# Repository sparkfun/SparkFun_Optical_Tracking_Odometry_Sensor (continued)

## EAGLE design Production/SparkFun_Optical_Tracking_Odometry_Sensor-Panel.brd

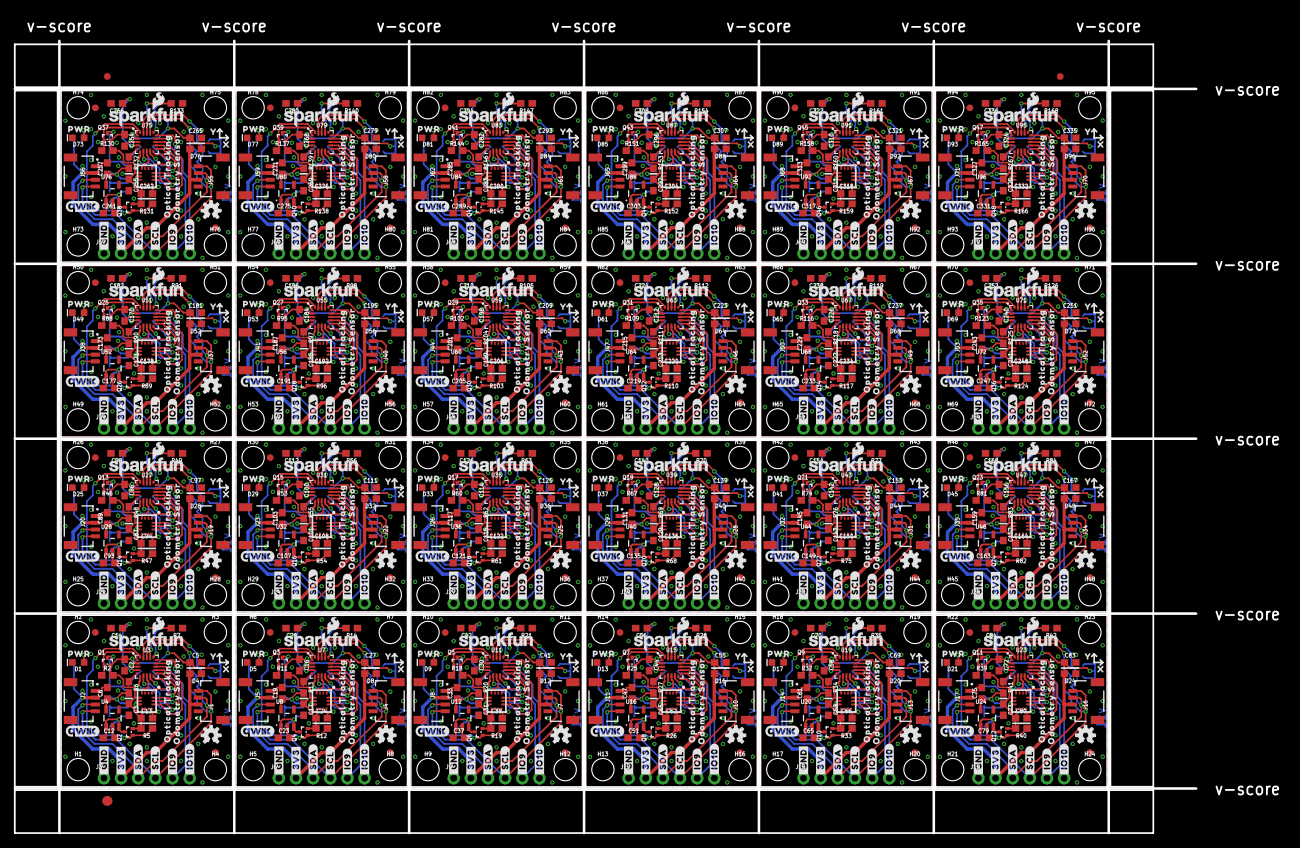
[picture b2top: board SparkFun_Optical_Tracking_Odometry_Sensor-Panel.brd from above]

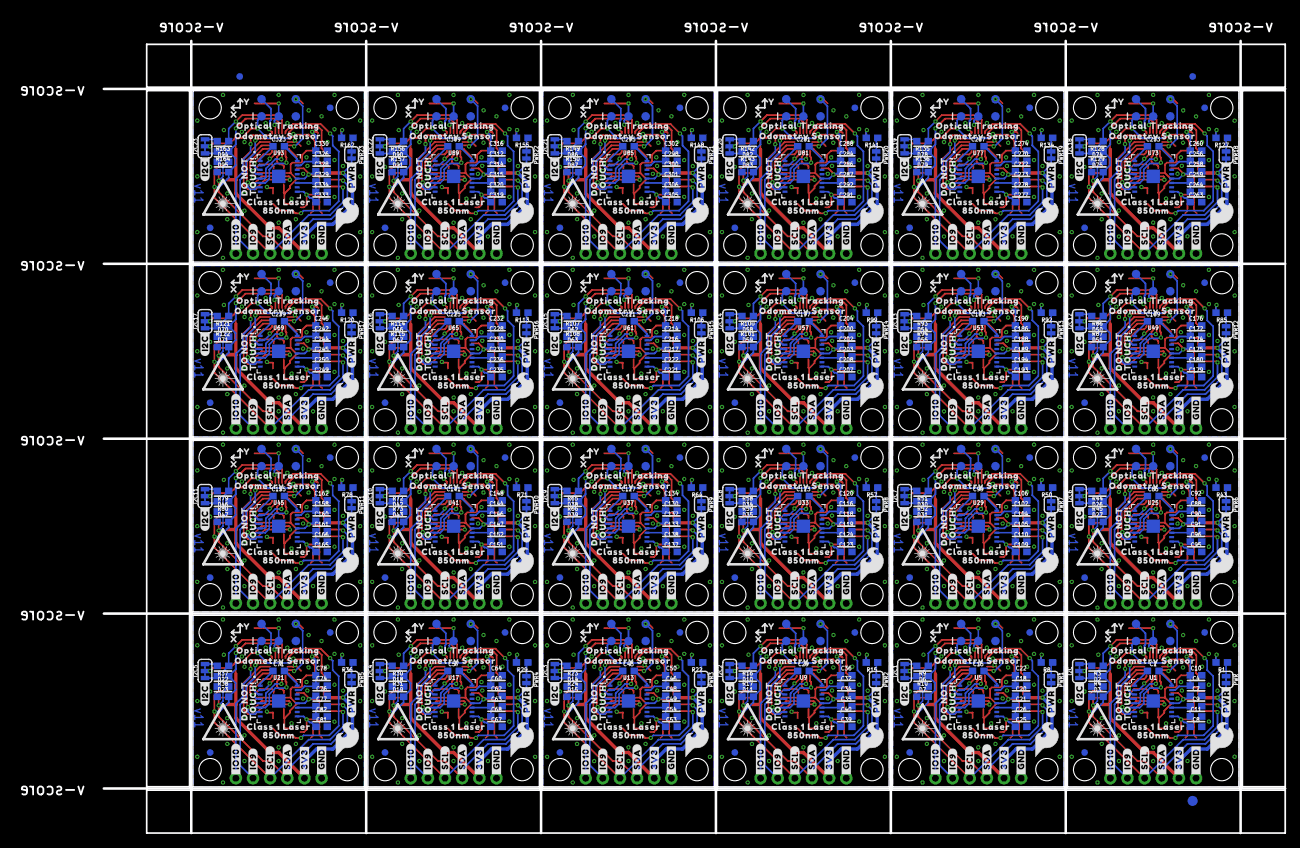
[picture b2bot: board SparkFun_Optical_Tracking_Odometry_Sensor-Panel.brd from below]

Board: 2 copper layers, 175.0 x 117.3 mm, 1830 parts (843 on the bottom side), 720 nets.

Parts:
C1, C15, C29, C43, C57, C71, C85, C99, C113, C127, C141, C155, C169, C183, C197, C211, C225, C239, C253, C267, C281, C295, C309, C323: 470pF; 0603
C2, C3, C4, C7, C8, C9, C13, C14, C16, C17, C18, C20, C21, C24, C25, C28, C30, C31, C32, C34, C35, C38, C39, C42, C44, C45, C46, C48, C49, C52, C53, C56, C58, C59, C60, C62, C63, C66, C67, C70, C72, C73, C74, C76, C77, C80, C81, C84, C86, C87, C88, C90, C91, C94, C95, C98, C100, C101, C102, C104, C105, C108, C109, C112, C114, C115, C116, C118, C119, C122, C123, C126, C128, C129, C130, C132, C133, C136, C137, C140, C142, C143, C144, C146, C147, C150, C151, C154, C156, C157, C158, C160, C161, C164, C165, C168, C170, C171, C172, C174, C175, C178, C179, C182, C184, C185, C186, C188, C189, C192, C193, C196, C198, C199, C200, C202, C203, C206, C207, C210, C212, C213, C214, C216, C217, C220, C221, C224, C226, C227, C228, C230, C231, C234, C235, C238, C240, C241, C242, C244, C245, C248, C249, C252, C254, C255, C256, C258, C259, C262, C263, C266, C268, C269, C270, C272, C273, C276, C277, C280, C282, C283, C284, C286, C287, C290, C291, C294, C296, C297, C298, C300, C301, C304, C305, C308, C310, C311, C312, C314, C315, C318, C319, C322, C324, C325, C326, C328, C329, C332, C333, C336: 0.1uF; 0603
C5, C6, C12, C19, C23, C27, C33, C37, C41, C47, C51, C55, C61, C65, C69, C75, C79, C83, C89, C93, C97, C103, C107, C111, C117, C121, C125, C131, C135, C139, C145, C149, C153, C159, C163, C167, C173, C177, C181, C187, C191, C195, C201, C205, C209, C215, C219, C223, C229, C233, C237, C243, C247, C251, C257, C261, C265, C271, C275, C279, C285, C289, C293, C299, C303, C307, C313, C317, C321, C327, C331, C335: 22uF; 0603
C10, C11, C22, C26, C36, C40, C50, C54, C64, C68, C78, C82, C92, C96, C106, C110, C120, C124, C134, C138, C148, C152, C162, C166, C176, C180, C190, C194, C204, C208, C218, C222, C232, C236, C246, C250, C260, C264, C274, C278, C288, C292, C302, C306, C316, C320, C330, C334: 4.7uF; 0603
D1, D5, D9, D13, D17, D21, D25, D29, D33, D37, D41, D45, D49, D53, D57, D61, D65, D69, D73, D77, D81, D85, D89, D93: Red; LED-0603
D2, D3, D4, D6, D7, D8, D10, D11, D12, D14, D15, D16, D18, D19, D20, D22, D23, D24, D26, D27, D28, D30, D31, D32, D34, D35, D36, D38, D39, D40, D42, D43, D44, D46, D47, D48, D50, D51, D52, D54, D55, D56, D58, D59, D60, D62, D63, D64, D66, D67, D68, D70, D71, D72, D74, D75, D76, D78, D79, D80, D82, D83, D84, D86, D87, D88, D90, D91, D92, D94, D95, D96: 24V; 0603
E$1, E$2, E$3, E$4: FIDUCIAL-1X2
E$5, E$6: FIDUCIAL-1.5X3
FD1, FD2, FD3, FD4, FD5, FD6, FD7, FD8, FD9, FD10, FD11, FD12, FD13, FD14, FD15, FD16, FD17, FD18, FD19, FD20, FD21, FD22, FD23, FD24, FD25, FD26, FD27, FD28, FD29, FD30, FD31, FD32, FD33, FD34, FD35, FD36, FD37, FD38, FD39, FD40, FD41, FD42, FD43, FD44, FD45, FD46, FD47, FD48, FD49, FD50, FD51, FD52, FD53, FD54, FD55, FD56, FD57, FD58, FD59, FD60, FD61, FD62, FD63, FD64, FD65, FD66, FD67, FD68, FD69, FD70, FD71, FD72, FD73, FD74, FD75, FD76, FD77, FD78, FD79, FD80, FD81, FD82, FD83, FD84, FD85, FD86, FD87, FD88, FD89, FD90, FD91, FD92, FD93, FD94, FD95, FD96: FIDUCIAL1X2; FIDUCIAL-1X2
H1, H2, H3, H4, H5, H6, H7, H8, H9, H10, H11, H12, H13, H14, H15, H16, H17, H18, H19, H20, H21, H22, H23, H24, H25, H26, H27, H28, H29, H30, H31, H32, H33, H34, H35, H36, H37, H38, H39, H40, H41, H42, H43, H44, H45, H46, H47, H48, H49, H50, H51, H52, H53, H54, H55, H56, H57, H58, H59, H60, H61, H62, H63, H64, H65, H66, H67, H68, H69, H70, H71, H72, H73, H74, H75, H76, H77, H78, H79, H80, H81, H82, H83, H84, H85, H86, H87, H88, H89, H90, H91, H92, H93, H94, H95, H96: STAND-OFF
I2C, I2C1, I2C2, I2C3, I2C4, I2C5, I2C6, I2C7, I2C8, I2C9, I2C10, I2C11, I2C12, I2C13, I2C14, I2C15, I2C16, I2C17, I2C18, I2C19, I2C20, I2C21, I2C22, I2C23: JUMPER-SMT_3_2-NC_TRACE_SILK; SMT-JUMPER_3_2-NC_TRACE_SILK
J1, J2, J4, J5, J7, J8, J10, J11, J13, J14, J16, J17, J19, J20, J22, J23, J25, J26, J28, J29, J31, J32, J34, J35, J37, J38, J40, J41, J43, J44, J46, J47, J49, J50, J52, J53, J55, J56, J58, J59, J61, J62, J64, J65, J67, J68, J70, J71: QWIIC_RIGHT_ANGLE; JST04_1MM_RA
J3, J6, J9, J12, J15, J18, J21, J24, J27, J30, J33, J36, J39, J42, J45, J48, J51, J54, J57, J60, J63, J66, J69, J72: 1X06_NO_SILK
LOGO1, LOGO4, LOGO7, LOGO10, LOGO13, LOGO16, LOGO19, LOGO22, LOGO25, LOGO28, LOGO31, LOGO34, LOGO37, LOGO40, LOGO43, LOGO46, LOGO49, LOGO52, LOGO55, LOGO58, LOGO61, LOGO64, LOGO67, LOGO70: OSHW-LOGOS; OSHW-LOGO-S
LOGO2, LOGO5, LOGO8, LOGO11, LOGO14, LOGO17, LOGO20, LOGO23, LOGO26, LOGO29, LOGO32, LOGO35, LOGO38, LOGO41, LOGO44, LOGO47, LOGO50, LOGO53, LOGO56, LOGO59, LOGO62, LOGO65, LOGO68, LOGO71: QWIIC_LOGO_5MM; QWIIC_5MM
LOGO3, LOGO6, LOGO9, LOGO12, LOGO15, LOGO18, LOGO21, LOGO24, LOGO27, LOGO30, LOGO33, LOGO36, LOGO39, LOGO42, LOGO45, LOGO48, LOGO51, LOGO54, LOGO57, LOGO60, LOGO63, LOGO66, LOGO69, LOGO72: SFE_LOGO_NAME_FLAME.1_INCH; SFE_LOGO_NAME_FLAME_.1
PWR, PWR1, PWR2, PWR3, PWR4, PWR5, PWR6, PWR7, PWR8, PWR9, PWR10, PWR11, PWR12, PWR13, PWR14, PWR15, PWR16, PWR17, PWR18, PWR19, PWR20, PWR21, PWR22, PWR23: JUMPER-SMT_2_NC_TRACE_SILK; SMT-JUMPER_2_NC_TRACE_SILK
Q1, Q2, Q3, Q4, Q5, Q6, Q7, Q8, Q9, Q10, Q11, Q12, Q13, Q14, Q15, Q16, Q17, Q18, Q19, Q20, Q21, Q22, Q23, Q24, Q25, Q26, Q27, Q28, Q29, Q30, Q31, Q32, Q33, Q34, Q35, Q36, Q37, Q38, Q39, Q40, Q41, Q42, Q43, Q44, Q45, Q46, Q47, Q48: 100mA/20V/3.8Ω; SOT-416FL
R1, R8, R15, R22, R29, R36, R43, R50, R57, R64, R71, R78, R85, R92, R99, R106, R113, R120, R127, R134, R141, R148, R155, R162: 4.7k; 0603
R2, R5, R7, R11, R12, R14, R18, R19, R21, R25, R26, R28, R32, R33, R35, R39, R40, R42, R46, R47, R49, R53, R54, R56, R60, R61, R63, R67, R68, R70, R74, R75, R77, R81, R82, R84, R88, R89, R91, R95, R96, R98, R102, R103, R105, R109, R110, R112, R116, R117, R119, R123, R124, R126, R130, R131, R133, R137, R138, R140, R144, R145, R147, R151, R152, R154, R158, R159, R161, R165, R166, R168: 100k; 0603
R3, R4, R9, R10, R16, R17, R23, R24, R30, R31, R37, R38, R44, R45, R51, R52, R58, R59, R65, R66, R72, R73, R79, R80, R86, R87, R93, R94, R100, R101, R107, R108, R114, R115, R121, R122, R128, R129, R135, R136, R142, R143, R149, R150, R156, R157, R163, R164: 2.2k; 0603
R6, R13, R20, R27, R34, R41, R48, R55, R62, R69, R76, R83, R90, R97, R104, R111, R118, R125, R132, R139, R146, R153, R160, R167: 1k; 0603
U1, U5, U9, U13, U17, U21, U25, U29, U33, U37, U41, U45, U49, U53, U57, U61, U65, U69, U73, U77, U81, U85, U89, U93: PAA5160E1-Q
U2, U6, U10, U14, U18, U22, U26, U30, U34, U38, U42, U46, U50, U54, U58, U62, U66, U70, U74, U78, U82, U86, U90, U94: LSM6DS0; LGA14L
U3, U7, U11, U15, U19, U23, U27, U31, U35, U39, U43, U47, U51, U55, U59, U63, U67, U71, U75, U79, U83, U87, U91, U95: STM32C011F6U6
U4, U8, U12, U16, U20, U24, U28, U32, U36, U40, U44, U48, U52, U56, U60, U64, U68, U72, U76, U80, U84, U88, U92, U96: RT9080-18GJ5; SOT23-5
U$1, U$13, U$59, U$88, U$117, U$146, U$175, U$204, U$233, U$262, U$291, U$320, U$349, U$378, U$407, U$436, U$465, U$494, U$523, U$552, U$581, U$610, U$639, U$668: PAD_05_03X2_TP_NO4
U$2, U$8, U$19, U$35, U$60, U$64, U$89, U$93, U$118, U$122, U$147, U$151, U$176, U$180, U$205, U$209, U$234, U$238, U$263, U$267, U$292, U$296, U$321, U$325, U$350, U$354, U$379, U$383, U$408, U$412, U$437, U$441, U$466, U$470, U$495, U$499, U$524, U$528, U$553, U$557, U$582, U$586, U$611, U$615, U$640, U$644, U$669, U$673: #_GND#0
U$3, U$9, U$27, U$36, U$61, U$65, U$90, U$94, U$119, U$123, U$148, U$152, U$177, U$181, U$206, U$210, U$235, U$239, U$264, U$268, U$293, U$297, U$322, U$326, U$351, U$355, U$380, U$384, U$409, U$413, U$438, U$442, U$467, U$471, U$496, U$500, U$525, U$529, U$554, U$558, U$583, U$587, U$612, U$616, U$641, U$645, U$670, U$674: #_3V3#0
U$4, U$10, U$33, U$37, U$62, U$66, U$91, U$95, U$120, U$124, U$149, U$153, U$178, U$182, U$207, U$211, U$236, U$240, U$265, U$269, U$294, U$298, U$323, U$327, U$352, U$356, U$381, U$385, U$410, U$414, U$439, U$443, U$468, U$472, U$497, U$501, U$526, U$530, U$555, U$559, U$584, U$588, U$613, U$617, U$642, U$646, U$671, U$675: #_SDA#0
U$5, U$11, U$34, U$38, U$63, U$67, U$92, U$96, U$121, U$125, U$150, U$154, U$179, U$183, U$208, U$212, U$237, U$241, U$266, U$270, U$295, U$299, U$324, U$328, U$353, U$357, U$382, U$386, U$411, U$415, U$440, U$444, U$469, U$473, U$498, U$502, U$527, U$531, U$556, U$560, U$585, U$589, U$614, U$618, U$643, U$647, U$672, U$676: #_SCL#0
U$6, U$54, U$83, U$112, U$141, U$170, U$199, U$228, U$257, U$286, U$315, U$344, U$373, U$402, U$431, U$460, U$489, U$518, U$547, U$576, U$605, U$634, U$663, U$692: CLASS_1_LASER0
U$7, U$23, U$56, U$57, U$85, U$86, U$114, U$115, U$143, U$144, U$172, U$173, U$201, U$202, U$230, U$231, U$259, U$260, U$288, U$289, U$317, U$318, U$346, U$347, U$375, U$376, U$404, U$405, U$433, U$434, U$462, U$463, U$491, U$492, U$520, U$521, U$549, U$550, U$578, U$579, U$607, U$608, U$636, U$637, U$665, U$666, U$694, U$695: #_IO10#0
U$12, U$32, U$55, U$58, U$84, U$87, U$113, U$116, U$142, U$145, U$171, U$174, U$200, U$203, U$229, U$232, U$258, U$261, U$287, U$290, U$316, U$319, U$345, U$348, U$374, U$377, U$403, U$406, U$432, U$435, U$461, U$464, U$490, U$493, U$519, U$522, U$548, U$551, U$577, U$580, U$606, U$609, U$635, U$638, U$664, U$667, U$693, U$696: #_IO9#0
U$14, U$16, U$39, U$41, U$68, U$70, U$97, U$99, U$126, U$128, U$155, U$157, U$184, U$186, U$213, U$215, U$242, U$244, U$271, U$273, U$300, U$302, U$329, U$331, U$358, U$360, U$387, U$389, U$416, U$418, U$445, U$447, U$474, U$476, U$503, U$505, U$532, U$534, U$561, U$563, U$590, U$592, U$619, U$621, U$648, U$650, U$677, U$679: OPTICAL_TRACKING0
U$15, U$17, U$40, U$42, U$69, U$71, U$98, U$100, U$127, U$129, U$156, U$158, U$185, U$187, U$214, U$216, U$243, U$245, U$272, U$274, U$301, U$303, U$330, U$332, U$359, U$361, U$388, U$390, U$417, U$419, U$446, U$448, U$475, U$477, U$504, U$506, U$533, U$535, U$562, U$564, U$591, U$593, U$620, U$622, U$649, U$651, U$678, U$680: ODOMETRY_SENSOR0
U$18, U$30, U$50, U$52, U$79, U$81, U$108, U$110, U$137, U$139, U$166, U$168, U$195, U$197, U$224, U$226, U$253, U$255, U$282, U$284, U$311, U$313, U$340, U$342, U$369, U$371, U$398, U$400, U$427, U$429, U$456, U$458, U$485, U$487, U$514, U$516, U$543, U$545, U$572, U$574, U$601, U$603, U$630, U$632, U$659, U$661, U$688, U$690: X0
U$20, U$43, U$72, U$101, U$130, U$159, U$188, U$217, U$246, U$275, U$304, U$333, U$362, U$391, U$420, U$449, U$478, U$507, U$536, U$565, U$594, U$623, U$652, U$681: #PWR#0
U$21, U$44, U$73, U$102, U$131, U$160, U$189, U$218, U$247, U$276, U$305, U$334, U$363, U$392, U$421, U$450, U$479, U$508, U$537, U$566, U$595, U$624, U$653, U$682: TOUCH##0
U$22, U$45, U$74, U$103, U$132, U$161, U$190, U$219, U$248, U$277, U$306, U$335, U$364, U$393, U$422, U$451, U$480, U$509, U$538, U$567, U$596, U$625, U$654, U$683: DO_NOT0
U$24, U$46, U$75, U$104, U$133, U$162, U$191, U$220, U$249, U$278, U$307, U$336, U$365, U$394, U$423, U$452, U$481, U$510, U$539, U$568, U$597, U$626, U$655, U$684: SFE_LOGO_FLAME_.2
U$25, U$47, U$76, U$105, U$134, U$163, U$192, U$221, U$250, U$279, U$308, U$337, U$366, U$395, U$424, U$453, U$482, U$511, U$540, U$569, U$598, U$627, U$656, U$685: PWR0
U$26, U$48, U$77, U$106, U$135, U$164, U$193, U$222, U$251, U$280, U$309, U$338, U$367, U$396, U$425, U$454, U$483, U$512, U$541, U$570, U$599, U$628, U$657, U$686: #I2C#0
U$28, U$49, U$78, U$107, U$136, U$165, U$194, U$223, U$252, U$281, U$310, U$339, U$368, U$397, U$426, U$455, U$484, U$513, U$542, U$571, U$600, U$629, U$658, U$687: 850NM0
U$29, U$31, U$51, U$53, U$80, U$82, U$109, U$111, U$138, U$140, U$167, U$169, U$196, U$198, U$225, U$227, U$254, U$256, U$283, U$285, U$312, U$314, U$341, U$343, U$370, U$372, U$399, U$401, U$428, U$430, U$457, U$459, U$486, U$488, U$515, U$517, U$544, U$546, U$573, U$575, U$602, U$604, U$631, U$633, U$660, U$662, U$689, U$691: Y0

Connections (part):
1.8V: C6.1, C7.1, R6.2, U1.12, U4.5
1.8V1: C19.1, C20.1, R13.2, U5.12, U8.5
1.8V2: C33.1, C34.1, R20.2, U9.12, U12.5
1.8V3: C47.1, C48.1, R27.2, U13.12, U16.5
1.8V4: C61.1, C62.1, R34.2, U17.12, U20.5
1.8V5: C75.1, C76.1, R41.2, U21.12, U24.5
1.8V6: C89.1, C90.1, R48.2, U25.12, U28.5
1.8V7: C103.1, C104.1, R55.2, U29.12, U32.5
1.8V8: C117.1, C118.1, R62.2, U33.12, U36.5
1.8V9: C131.1, C132.1, R69.2, U37.12, U40.5
1.8V10: C145.1, C146.1, R76.2, U41.12, U44.5
1.8V11: C159.1, C160.1, R83.2, U45.12, U48.5
1.8V12: C173.1, C174.1, R90.2, U49.12, U52.5
1.8V13: C187.1, C188.1, R97.2, U53.12, U56.5
1.8V14: C201.1, C202.1, R104.2, U57.12, U60.5
1.8V15: C215.1, C216.1, R111.2, U61.12, U64.5
1.8V16: C229.1, C230.1, R118.2, U65.12, U68.5
1.8V17: C243.1, C244.1, R125.2, U69.12, U72.5
1.8V18: C257.1, C258.1, R132.2, U73.12, U76.5
1.8V19: C271.1, C272.1, R139.2, U77.12, U80.5
1.8V20: C285.1, C286.1, R146.2, U81.12, U84.5
1.8V21: C299.1, C300.1, R153.2, U85.12, U88.5
1.8V22: C313.1, C314.1, R160.2, U89.12, U92.5
1.8V23: C327.1, C328.1, R167.2, U93.12, U96.5
3.3V: C2.1, C3.1, C5.1, C13.1, D4.2, I2C.2, J1.2, J2.2, J3.2, PWR.2, Q1.2, Q2.2, R2.2, R5.2, U2.5, U2.8, U3.2, U$1.1
3.3V1: C16.1, C17.1, C24.1, C27.1, D8.2, I2C1.2, J4.2, J5.2, J6.2, PWR1.2, Q3.2, Q4.2, R11.2, R12.2, U6.5, U6.8, U7.2, U$13.1
3.3V2: C30.1, C31.1, C38.1, C41.1, D12.2, I2C2.2, J7.2, J8.2, J9.2, PWR2.2, Q5.2, Q6.2, R18.2, R19.2, U10.5, U10.8, U11.2, U$59.1
3.3V3: C44.1, C45.1, C52.1, C55.1, D16.2, I2C3.2, J10.2, J11.2, J12.2, PWR3.2, Q7.2, Q8.2, R25.2, R26.2, U14.5, U14.8, U15.2, U$88.1
3.3V4: C58.1, C59.1, C66.1, C69.1, D20.2, I2C4.2, J13.2, J14.2, J15.2, PWR4.2, Q9.2, Q10.2, R32.2, R33.2, U18.5, U18.8, U19.2, U$117.1
3.3V5: C72.1, C73.1, C80.1, C83.1, D24.2, I2C5.2, J16.2, J17.2, J18.2, PWR5.2, Q11.2, Q12.2, R39.2, R40.2, U22.5, U22.8, U23.2, U$146.1
3.3V6: C86.1, C87.1, C94.1, C97.1, D28.2, I2C6.2, J19.2, J20.2, J21.2, PWR6.2, Q13.2, Q14.2, R46.2, R47.2, U26.5, U26.8, U27.2, U$175.1
3.3V7: C100.1, C101.1, C108.1, C111.1, D32.2, I2C7.2, J22.2, J23.2, J24.2, PWR7.2, Q15.2, Q16.2, R53.2, R54.2, U30.5, U30.8, U31.2, U$204.1
3.3V8: C114.1, C115.1, C122.1, C125.1, D36.2, I2C8.2, J25.2, J26.2, J27.2, PWR8.2, Q17.2, Q18.2, R60.2, R61.2, U34.5, U34.8, U35.2, U$233.1
3.3V9: C128.1, C129.1, C136.1, C139.1, D40.2, I2C9.2, J28.2, J29.2, J30.2, PWR9.2, Q19.2, Q20.2, R67.2, R68.2, U38.5, U38.8, U39.2, U$262.1
3.3V10: C142.1, C143.1, C150.1, C153.1, D44.2, I2C10.2, J31.2, J32.2, J33.2, PWR10.2, Q21.2, Q22.2, R74.2, R75.2, U42.5, U42.8, U43.2, U$291.1
3.3V11: C156.1, C157.1, C164.1, C167.1, D48.2, I2C11.2, J34.2, J35.2, J36.2, PWR11.2, Q23.2, Q24.2, R81.2, R82.2, U46.5, U46.8, U47.2, U$320.1
3.3V12: C170.1, C171.1, C178.1, C181.1, D52.2, I2C12.2, J37.2, J38.2, J39.2, PWR12.2, Q25.2, Q26.2, R88.2, R89.2, U50.5, U50.8, U51.2, U$349.1
3.3V13: C184.1, C185.1, C192.1, C195.1, D56.2, I2C13.2, J40.2, J41.2, J42.2, PWR13.2, Q27.2, Q28.2, R95.2, R96.2, U54.5, U54.8, U55.2, U$378.1
3.3V14: C198.1, C199.1, C206.1, C209.1, D60.2, I2C14.2, J43.2, J44.2, J45.2, PWR14.2, Q29.2, Q30.2, R102.2, R103.2, U58.5, U58.8, U59.2, U$407.1
3.3V15: C212.1, C213.1, C220.1, C223.1, D64.2, I2C15.2, J46.2, J47.2, J48.2, PWR15.2, Q31.2, Q32.2, R109.2, R110.2, U62.5, U62.8, U63.2, U$436.1
3.3V16: C226.1, C227.1, C234.1, C237.1, D68.2, I2C16.2, J49.2, J50.2, J51.2, PWR16.2, Q33.2, Q34.2, R116.2, R117.2, U66.5, U66.8, U67.2, U$465.1
3.3V17: C240.1, C241.1, C248.1, C251.1, D72.2, I2C17.2, J52.2, J53.2, J54.2, PWR17.2, Q35.2, Q36.2, R123.2, R124.2, U70.5, U70.8, U71.2, U$494.1
3.3V18: C254.1, C255.1, C262.1, C265.1, D76.2, I2C18.2, J55.2, J56.2, J57.2, PWR18.2, Q37.2, Q38.2, R130.2, R131.2, U74.5, U74.8, U75.2, U$523.1
3.3V19: C268.1, C269.1, C276.1, C279.1, D80.2, I2C19.2, J58.2, J59.2, J60.2, PWR19.2, Q39.2, Q40.2, R137.2, R138.2, U78.5, U78.8, U79.2, U$552.1
3.3V20: C282.1, C283.1, C290.1, C293.1, D84.2, I2C20.2, J61.2, J62.2, J63.2, PWR20.2, Q41.2, Q42.2, R144.2, R145.2, U82.5, U82.8, U83.2, U$581.1
3.3V21: C296.1, C297.1, C304.1, C307.1, D88.2, I2C21.2, J64.2, J65.2, J66.2, PWR21.2, Q43.2, Q44.2, R151.2, R152.2, U86.5, U86.8, U87.2, U$610.1
3.3V22: C310.1, C311.1, C318.1, C321.1, D92.2, I2C22.2, J67.2, J68.2, J69.2, PWR22.2, Q45.2, Q46.2, R158.2, R159.2, U90.5, U90.8, U91.2, U$639.1
3.3V23: C324.1, C325.1, C332.1, C335.1, D96.2, I2C23.2, J70.2, J71.2, J72.2, PWR23.2, Q47.2, Q48.2, R165.2, R166.2, U94.5, U94.8, U95.2, U$668.1
3.3V_SW: C8.1, C12.1, Q2.3, U1.9, U4.1, U4.3
3.3V_SW1: C18.1, C22.1, Q3.3, U5.15
3.3V_SW2: C4.1, C10.1, Q1.3, U1.15
3.3V_SW3: C23.1, C25.1, Q4.3, U5.9, U8.1, U8.3
3.3V_SW4: C32.1, C36.1, Q5.3, U9.15
3.3V_SW5: C37.1, C39.1, Q6.3, U9.9, U12.1, U12.3
3.3V_SW6: C46.1, C50.1, Q7.3, U13.15
3.3V_SW7: C51.1, C53.1, Q8.3, U13.9, U16.1, U16.3
3.3V_SW8: C60.1, C64.1, Q9.3, U17.15
3.3V_SW9: C65.1, C67.1, Q10.3, U17.9, U20.1, U20.3
3.3V_SW10: C74.1, C78.1, Q11.3, U21.15
3.3V_SW11: C79.1, C81.1, Q12.3, U21.9, U24.1, U24.3
3.3V_SW12: C88.1, C92.1, Q13.3, U25.15
3.3V_SW13: C93.1, C95.1, Q14.3, U25.9, U28.1, U28.3
3.3V_SW14: C102.1, C106.1, Q15.3, U29.15
3.3V_SW15: C107.1, C109.1, Q16.3, U29.9, U32.1, U32.3
3.3V_SW16: C116.1, C120.1, Q17.3, U33.15
3.3V_SW17: C121.1, C123.1, Q18.3, U33.9, U36.1, U36.3
3.3V_SW18: C130.1, C134.1, Q19.3, U37.15
3.3V_SW19: C135.1, C137.1, Q20.3, U37.9, U40.1, U40.3
3.3V_SW20: C144.1, C148.1, Q21.3, U41.15
3.3V_SW21: C149.1, C151.1, Q22.3, U41.9, U44.1, U44.3
3.3V_SW22: C158.1, C162.1, Q23.3, U45.15
3.3V_SW23: C163.1, C165.1, Q24.3, U45.9, U48.1, U48.3
3.3V_SW24: C172.1, C176.1, Q25.3, U49.15
3.3V_SW25: C177.1, C179.1, Q26.3, U49.9, U52.1, U52.3
3.3V_SW26: C186.1, C190.1, Q27.3, U53.15
3.3V_SW27: C191.1, C193.1, Q28.3, U53.9, U56.1, U56.3
3.3V_SW28: C200.1, C204.1, Q29.3, U57.15
3.3V_SW29: C205.1, C207.1, Q30.3, U57.9, U60.1, U60.3
3.3V_SW30: C214.1, C218.1, Q31.3, U61.15
3.3V_SW31: C219.1, C221.1, Q32.3, U61.9, U64.1, U64.3
3.3V_SW32: C228.1, C232.1, Q33.3, U65.15
3.3V_SW33: C233.1, C235.1, Q34.3, U65.9, U68.1, U68.3
3.3V_SW34: C242.1, C246.1, Q35.3, U69.15
3.3V_SW35: C247.1, C249.1, Q36.3, U69.9, U72.1, U72.3
3.3V_SW36: C256.1, C260.1, Q37.3, U73.15
3.3V_SW37: C261.1, C263.1, Q38.3, U73.9, U76.1, U76.3
3.3V_SW38: C270.1, C274.1, Q39.3, U77.15
3.3V_SW39: C275.1, C277.1, Q40.3, U77.9, U80.1, U80.3
3.3V_SW40: C284.1, C288.1, Q41.3, U81.15
3.3V_SW41: C289.1, C291.1, Q42.3, U81.9, U84.1, U84.3
3.3V_SW42: C298.1, C302.1, Q43.3, U85.15
3.3V_SW43: C303.1, C305.1, Q44.3, U85.9, U88.1, U88.3
3.3V_SW44: C312.1, C316.1, Q45.3, U89.15
3.3V_SW45: C317.1, C319.1, Q46.3, U89.9, U92.1, U92.3
3.3V_SW46: C326.1, C330.1, Q47.3, U93.15
3.3V_SW47: C331.1, C333.1, Q48.3, U93.9, U96.1, U96.3
!PAA_POW!: Q2.1, R5.1, U3.20
!PAA_POW!1: Q4.1, R12.1, U7.20
!PAA_POW!2: Q6.1, R19.1, U11.20
!PAA_POW!3: Q8.1, R26.1, U15.20
!PAA_POW!4: Q10.1, R33.1, U19.20
!PAA_POW!5: Q12.1, R40.1, U23.20
!PAA_POW!6: Q14.1, R47.1, U27.20
!PAA_POW!7: Q16.1, R54.1, U31.20
!PAA_POW!8: Q18.1, R61.1, U35.20
!PAA_POW!9: Q20.1, R68.1, U39.20
!PAA_POW!10: Q22.1, R75.1, U43.20
!PAA_POW!11: Q24.1, R82.1, U47.20
!PAA_POW!12: Q26.1, R89.1, U51.20
!PAA_POW!13: Q28.1, R96.1, U55.20
!PAA_POW!14: Q30.1, R103.1, U59.20
!PAA_POW!15: Q32.1, R110.1, U63.20
!PAA_POW!16: Q34.1, R117.1, U67.20
!PAA_POW!17: Q36.1, R124.1, U71.20
!PAA_POW!18: Q38.1, R131.1, U75.20
!PAA_POW!19: Q40.1, R138.1, U79.20
!PAA_POW!20: Q42.1, R145.1, U83.20
!PAA_POW!21: Q44.1, R152.1, U87.20
!PAA_POW!22: Q46.1, R159.1, U91.20
!PAA_POW!23: Q48.1, R166.1, U95.20
!VCSEL_POW!: Q1.1, R2.1, U3.1
!VCSEL_POW!1: Q3.1, R11.1, U7.1
!VCSEL_POW!2: Q5.1, R18.1, U11.1
!VCSEL_POW!3: Q7.1, R25.1, U15.1
!VCSEL_POW!4: Q9.1, R32.1, U19.1
!VCSEL_POW!5: Q11.1, R39.1, U23.1
!VCSEL_POW!6: Q13.1, R46.1, U27.1
!VCSEL_POW!7: Q15.1, R53.1, U31.1
!VCSEL_POW!8: Q17.1, R60.1, U35.1
!VCSEL_POW!9: Q19.1, R67.1, U39.1
!VCSEL_POW!10: Q21.1, R74.1, U43.1
!VCSEL_POW!11: Q23.1, R81.1, U47.1
!VCSEL_POW!12: Q25.1, R88.1, U51.1
!VCSEL_POW!13: Q27.1, R95.1, U55.1
!VCSEL_POW!14: Q29.1, R102.1, U59.1
!VCSEL_POW!15: Q31.1, R109.1, U63.1
!VCSEL_POW!16: Q33.1, R116.1, U67.1
!VCSEL_POW!17: Q35.1, R123.1, U71.1
!VCSEL_POW!18: Q37.1, R130.1, U75.1
!VCSEL_POW!19: Q39.1, R137.1, U79.1
!VCSEL_POW!20: Q41.1, R144.1, U83.1
!VCSEL_POW!21: Q43.1, R151.1, U87.1
!VCSEL_POW!22: Q45.1, R158.1, U91.1
!VCSEL_POW!23: Q47.1, R165.1, U95.1
GND: C2.2, C3.2, C4.2, C5.2, C6.2, C7.2, C8.2, C9.2, C10.2, C11.2, C12.2, C13.2, C14.2, D1.C, D2.1, D3.1, D4.1, J1.1, J2.1, J3.1, R7.1, U1.8, U1.13, U1.17, U2.6, U2.7, U3.3, U4.2, U$1.5
GND1: C16.2, C17.2, C18.2, C19.2, C20.2, C21.2, C22.2, C23.2, C24.2, C25.2, C26.2, C27.2, C28.2, D5.C, D6.1, D7.1, D8.1, J4.1, J5.1, J6.1, R14.1, U5.8, U5.13, U5.17, U6.6, U6.7, U7.3, U8.2, U$13.5
GND2: C30.2, C31.2, C32.2, C33.2, C34.2, C35.2, C36.2, C37.2, C38.2, C39.2, C40.2, C41.2, C42.2, D9.C, D10.1, D11.1, D12.1, J7.1, J8.1, J9.1, R21.1, U9.8, U9.13, U9.17, U10.6, U10.7, U11.3, U12.2, U$59.5
GND3: C44.2, C45.2, C46.2, C47.2, C48.2, C49.2, C50.2, C51.2, C52.2, C53.2, C54.2, C55.2, C56.2, D13.C, D14.1, D15.1, D16.1, J10.1, J11.1, J12.1, R28.1, U13.8, U13.13, U13.17, U14.6, U14.7, U15.3, U16.2, U$88.5
GND4: C58.2, C59.2, C60.2, C61.2, C62.2, C63.2, C64.2, C65.2, C66.2, C67.2, C68.2, C69.2, C70.2, D17.C, D18.1, D19.1, D20.1, J13.1, J14.1, J15.1, R35.1, U17.8, U17.13, U17.17, U18.6, U18.7, U19.3, U20.2, U$117.5
GND5: C72.2, C73.2, C74.2, C75.2, C76.2, C77.2, C78.2, C79.2, C80.2, C81.2, C82.2, C83.2, C84.2, D21.C, D22.1, D23.1, D24.1, J16.1, J17.1, J18.1, R42.1, U21.8, U21.13, U21.17, U22.6, U22.7, U23.3, U24.2, U$146.5
GND6: C86.2, C87.2, C88.2, C89.2, C90.2, C91.2, C92.2, C93.2, C94.2, C95.2, C96.2, C97.2, C98.2, D25.C, D26.1, D27.1, D28.1, J19.1, J20.1, J21.1, R49.1, U25.8, U25.13, U25.17, U26.6, U26.7, U27.3, U28.2, U$175.5
GND7: C100.2, C101.2, C102.2, C103.2, C104.2, C105.2, C106.2, C107.2, C108.2, C109.2, C110.2, C111.2, C112.2, D29.C, D30.1, D31.1, D32.1, J22.1, J23.1, J24.1, R56.1, U29.8, U29.13, U29.17, U30.6, U30.7, U31.3, U32.2, U$204.5
GND8: C114.2, C115.2, C116.2, C117.2, C118.2, C119.2, C120.2, C121.2, C122.2, C123.2, C124.2, C125.2, C126.2, D33.C, D34.1, D35.1, D36.1, J25.1, J26.1, J27.1, R63.1, U33.8, U33.13, U33.17, U34.6, U34.7, U35.3, U36.2, U$233.5
GND9: C128.2, C129.2, C130.2, C131.2, C132.2, C133.2, C134.2, C135.2, C136.2, C137.2, C138.2, C139.2, C140.2, D37.C, D38.1, D39.1, D40.1, J28.1, J29.1, J30.1, R70.1, U37.8, U37.13, U37.17, U38.6, U38.7, U39.3, U40.2, U$262.5
GND10: C142.2, C143.2, C144.2, C145.2, C146.2, C147.2, C148.2, C149.2, C150.2, C151.2, C152.2, C153.2, C154.2, D41.C, D42.1, D43.1, D44.1, J31.1, J32.1, J33.1, R77.1, U41.8, U41.13, U41.17, U42.6, U42.7, U43.3, U44.2, U$291.5
GND11: C156.2, C157.2, C158.2, C159.2, C160.2, C161.2, C162.2, C163.2, C164.2, C165.2, C166.2, C167.2, C168.2, D45.C, D46.1, D47.1, D48.1, J34.1, J35.1, J36.1, R84.1, U45.8, U45.13, U45.17, U46.6, U46.7, U47.3, U48.2, U$320.5
GND12: C170.2, C171.2, C172.2, C173.2, C174.2, C175.2, C176.2, C177.2, C178.2, C179.2, C180.2, C181.2, C182.2, D49.C, D50.1, D51.1, D52.1, J37.1, J38.1, J39.1, R91.1, U49.8, U49.13, U49.17, U50.6, U50.7, U51.3, U52.2, U$349.5
GND13: C184.2, C185.2, C186.2, C187.2, C188.2, C189.2, C190.2, C191.2, C192.2, C193.2, C194.2, C195.2, C196.2, D53.C, D54.1, D55.1, D56.1, J40.1, J41.1, J42.1, R98.1, U53.8, U53.13, U53.17, U54.6, U54.7, U55.3, U56.2, U$378.5
GND14: C198.2, C199.2, C200.2, C201.2, C202.2, C203.2, C204.2, C205.2, C206.2, C207.2, C208.2, C209.2, C210.2, D57.C, D58.1, D59.1, D60.1, J43.1, J44.1, J45.1, R105.1, U57.8, U57.13, U57.17, U58.6, U58.7, U59.3, U60.2, U$407.5
GND15: C212.2, C213.2, C214.2, C215.2, C216.2, C217.2, C218.2, C219.2, C220.2, C221.2, C222.2, C223.2, C224.2, D61.C, D62.1, D63.1, D64.1, J46.1, J47.1, J48.1, R112.1, U61.8, U61.13, U61.17, U62.6, U62.7, U63.3, U64.2, U$436.5
GND16: C226.2, C227.2, C228.2, C229.2, C230.2, C231.2, C232.2, C233.2, C234.2, C235.2, C236.2, C237.2, C238.2, D65.C, D66.1, D67.1, D68.1, J49.1, J50.1, J51.1, R119.1, U65.8, U65.13, U65.17, U66.6, U66.7, U67.3, U68.2, U$465.5
GND17: C240.2, C241.2, C242.2, C243.2, C244.2, C245.2, C246.2, C247.2, C248.2, C249.2, C250.2, C251.2, C252.2, D69.C, D70.1, D71.1, D72.1, J52.1, J53.1, J54.1, R126.1, U69.8, U69.13, U69.17, U70.6, U70.7, U71.3, U72.2, U$494.5
GND18: C254.2, C255.2, C256.2, C257.2, C258.2, C259.2, C260.2, C261.2, C262.2, C263.2, C264.2, C265.2, C266.2, D73.C, D74.1, D75.1, D76.1, J55.1, J56.1, J57.1, R133.1, U73.8, U73.13, U73.17, U74.6, U74.7, U75.3, U76.2, U$523.5
GND19: C268.2, C269.2, C270.2, C271.2, C272.2, C273.2, C274.2, C275.2, C276.2, C277.2, C278.2, C279.2, C280.2, D77.C, D78.1, D79.1, D80.1, J58.1, J59.1, J60.1, R140.1, U77.8, U77.13, U77.17, U78.6, U78.7, U79.3, U80.2, U$552.5
GND20: C282.2, C283.2, C284.2, C285.2, C286.2, C287.2, C288.2, C289.2, C290.2, C291.2, C292.2, C293.2, C294.2, D81.C, D82.1, D83.1, D84.1, J61.1, J62.1, J63.1, R147.1, U81.8, U81.13, U81.17, U82.6, U82.7, U83.3, U84.2, U$581.5
GND21: C296.2, C297.2, C298.2, C299.2, C300.2, C301.2, C302.2, C303.2, C304.2, C305.2, C306.2, C307.2, C308.2, D85.C, D86.1, D87.1, D88.1, J64.1, J65.1, J66.1, R154.1, U85.8, U85.13, U85.17, U86.6, U86.7, U87.3, U88.2, U$610.5
GND22: C310.2, C311.2, C312.2, C313.2, C314.2, C315.2, C316.2, C317.2, C318.2, C319.2, C320.2, C321.2, C322.2, D89.C, D90.1, D91.1, D92.1, J67.1, J68.1, J69.1, R161.1, U89.8, U89.13, U89.17, U90.6, U90.7, U91.3, U92.2, U$639.5
GND23: C324.2, C325.2, C326.2, C327.2, C328.2, C329.2, C330.2, C331.2, C332.2, C333.2, C334.2, C335.2, C336.2, D93.C, D94.1, D95.1, D96.1, J70.1, J71.1, J72.1, R168.1, U93.8, U93.13, U93.17, U94.6, U94.7, U95.3, U96.2, U$668.5
LSM_!CS!: U2.12, U3.13
LSM_!CS!1: U6.12, U7.13
LSM_!CS!2: U10.12, U11.13
LSM_!CS!3: U14.12, U15.13
LSM_!CS!4: U18.12, U19.13
LSM_!CS!5: U22.12, U23.13
LSM_!CS!6: U26.12, U27.13
LSM_!CS!7: U30.12, U31.13
LSM_!CS!8: U34.12, U35.13
LSM_!CS!9: U38.12, U39.13
LSM_!CS!10: U42.12, U43.13
LSM_!CS!11: U46.12, U47.13
LSM_!CS!12: U50.12, U51.13
LSM_!CS!13: U54.12, U55.13
LSM_!CS!14: U58.12, U59.13
LSM_!CS!15: U62.12, U63.13
LSM_!CS!16: U66.12, U67.13
LSM_!CS!17: U70.12, U71.13
LSM_!CS!18: U74.12, U75.13
LSM_!CS!19: U78.12, U79.13
LSM_!CS!20: U82.12, U83.13
LSM_!CS!21: U86.12, U87.13
LSM_!CS!22: U90.12, U91.13
LSM_!CS!23: U94.12, U95.13
LSM_INT1: U2.4, U3.8
LSM_INT2: U6.4, U7.8
LSM_INT3: U10.4, U11.8
LSM_INT4: U14.4, U15.8
LSM_INT5: U18.4, U19.8
LSM_INT6: U22.4, U23.8
LSM_INT7: U26.4, U27.8
LSM_INT8: U30.4, U31.8
LSM_INT9: U34.4, U35.8
LSM_INT10: U38.4, U39.8
LSM_INT11: U42.4, U43.8
LSM_INT12: U46.4, U47.8
LSM_INT13: U50.4, U51.8
LSM_INT14: U54.4, U55.8
LSM_INT15: U58.4, U59.8
LSM_INT16: U62.4, U63.8
LSM_INT17: U66.4, U67.8
LSM_INT18: U70.4, U71.8
LSM_INT19: U74.4, U75.8
LSM_INT20: U78.4, U79.8
LSM_INT21: U82.4, U83.8
LSM_INT22: U86.4, U87.8
LSM_INT23: U90.4, U91.8
LSM_INT24: U94.4, U95.8
unnamed: PWR.1, R1.1
unnamed: D1.A, R1.2
unnamed: C1.1, U1.1
unnamed: C1.2, U1.16
unnamed: I2C.3, R3.2
unnamed: I2C.1, R4.2
unnamed: C9.1, C11.1, U1.11
unnamed: R6.1, U3.5
unnamed: C15.1, U5.1
unnamed: C15.2, U5.16
unnamed: I2C1.3, R9.2
unnamed: I2C1.1, R10.2
unnamed: C21.1, C26.1, U5.11
unnamed: R13.1, U7.5
unnamed: PWR1.1, R8.1
unnamed: D5.A, R8.2
unnamed: C29.1, U9.1
unnamed: C29.2, U9.16
unnamed: I2C2.3, R16.2
unnamed: I2C2.1, R17.2
unnamed: C35.1, C40.1, U9.11
unnamed: R20.1, U11.5
unnamed: PWR2.1, R15.1
unnamed: D9.A, R15.2
unnamed: C43.1, U13.1
unnamed: C43.2, U13.16
unnamed: I2C3.3, R23.2
unnamed: I2C3.1, R24.2
unnamed: C49.1, C54.1, U13.11
unnamed: R27.1, U15.5
unnamed: PWR3.1, R22.1
unnamed: D13.A, R22.2
unnamed: C57.1, U17.1
unnamed: C57.2, U17.16
unnamed: I2C4.3, R30.2
unnamed: I2C4.1, R31.2
unnamed: C63.1, C68.1, U17.11
unnamed: R34.1, U19.5
unnamed: PWR4.1, R29.1
unnamed: D17.A, R29.2
unnamed: C71.1, U21.1
unnamed: C71.2, U21.16
unnamed: I2C5.3, R37.2
unnamed: I2C5.1, R38.2
unnamed: C77.1, C82.1, U21.11
unnamed: R41.1, U23.5
unnamed: PWR5.1, R36.1
unnamed: D21.A, R36.2
unnamed: C85.1, U25.1
unnamed: C85.2, U25.16
unnamed: I2C6.3, R44.2
unnamed: I2C6.1, R45.2
unnamed: C91.1, C96.1, U25.11
unnamed: R48.1, U27.5
unnamed: PWR6.1, R43.1
unnamed: D25.A, R43.2
unnamed: C99.1, U29.1
unnamed: C99.2, U29.16
unnamed: I2C7.3, R51.2
unnamed: I2C7.1, R52.2
unnamed: C105.1, C110.1, U29.11
unnamed: R55.1, U31.5
unnamed: PWR7.1, R50.1
unnamed: D29.A, R50.2
unnamed: C113.1, U33.1
unnamed: C113.2, U33.16
unnamed: I2C8.3, R58.2
unnamed: I2C8.1, R59.2
unnamed: C119.1, C124.1, U33.11
unnamed: R62.1, U35.5
unnamed: PWR8.1, R57.1
unnamed: D33.A, R57.2
unnamed: C127.1, U37.1
unnamed: C127.2, U37.16
unnamed: I2C9.3, R65.2
unnamed: I2C9.1, R66.2
unnamed: C133.1, C138.1, U37.11
unnamed: R69.1, U39.5
unnamed: PWR9.1, R64.1
unnamed: D37.A, R64.2
unnamed: C141.1, U41.1
unnamed: C141.2, U41.16
unnamed: I2C10.3, R72.2
unnamed: I2C10.1, R73.2
unnamed: C147.1, C152.1, U41.11
unnamed: R76.1, U43.5
unnamed: PWR10.1, R71.1
unnamed: D41.A, R71.2
unnamed: C155.1, U45.1
unnamed: C155.2, U45.16
unnamed: I2C11.3, R79.2
unnamed: I2C11.1, R80.2
unnamed: C161.1, C166.1, U45.11
unnamed: R83.1, U47.5
unnamed: PWR11.1, R78.1
unnamed: D45.A, R78.2
unnamed: C169.1, U49.1
unnamed: C169.2, U49.16
unnamed: I2C12.3, R86.2
unnamed: I2C12.1, R87.2
unnamed: C175.1, C180.1, U49.11
unnamed: R90.1, U51.5
unnamed: PWR12.1, R85.1
unnamed: D49.A, R85.2
unnamed: C183.1, U53.1
unnamed: C183.2, U53.16
unnamed: I2C13.3, R93.2
unnamed: I2C13.1, R94.2
unnamed: C189.1, C194.1, U53.11
unnamed: R97.1, U55.5
unnamed: PWR13.1, R92.1
unnamed: D53.A, R92.2
unnamed: C197.1, U57.1
unnamed: C197.2, U57.16
unnamed: I2C14.3, R100.2
unnamed: I2C14.1, R101.2
unnamed: C203.1, C208.1, U57.11
unnamed: R104.1, U59.5
unnamed: PWR14.1, R99.1
unnamed: D57.A, R99.2
unnamed: C211.1, U61.1
unnamed: C211.2, U61.16
unnamed: I2C15.3, R107.2
unnamed: I2C15.1, R108.2
unnamed: C217.1, C222.1, U61.11
unnamed: R111.1, U63.5
unnamed: PWR15.1, R106.1
unnamed: D61.A, R106.2
unnamed: C225.1, U65.1
unnamed: C225.2, U65.16
unnamed: I2C16.3, R114.2
unnamed: I2C16.1, R115.2
unnamed: C231.1, C236.1, U65.11
unnamed: R118.1, U67.5
unnamed: PWR16.1, R113.1
unnamed: D65.A, R113.2
unnamed: C239.1, U69.1
unnamed: C239.2, U69.16
unnamed: I2C17.3, R121.2
unnamed: I2C17.1, R122.2
unnamed: C245.1, C250.1, U69.11
unnamed: R125.1, U71.5
unnamed: PWR17.1, R120.1
unnamed: D69.A, R120.2
unnamed: C253.1, U73.1
unnamed: C253.2, U73.16
unnamed: I2C18.3, R128.2
unnamed: I2C18.1, R129.2
unnamed: C259.1, C264.1, U73.11
unnamed: R132.1, U75.5
unnamed: PWR18.1, R127.1
unnamed: D73.A, R127.2
unnamed: C267.1, U77.1
unnamed: C267.2, U77.16
unnamed: I2C19.3, R135.2
unnamed: I2C19.1, R136.2
unnamed: C273.1, C278.1, U77.11
unnamed: R139.1, U79.5
unnamed: PWR19.1, R134.1
unnamed: D77.A, R134.2
unnamed: C281.1, U81.1
unnamed: C281.2, U81.16
unnamed: I2C20.3, R142.2
unnamed: I2C20.1, R143.2
unnamed: C287.1, C292.1, U81.11
unnamed: R146.1, U83.5
unnamed: PWR20.1, R141.1
unnamed: D81.A, R141.2
unnamed: C295.1, U85.1
unnamed: C295.2, U85.16
unnamed: I2C21.3, R149.2
unnamed: I2C21.1, R150.2
unnamed: C301.1, C306.1, U85.11
unnamed: R153.1, U87.5
unnamed: PWR21.1, R148.1
unnamed: D85.A, R148.2
unnamed: C309.1, U89.1
unnamed: C309.2, U89.16
unnamed: I2C22.3, R156.2
unnamed: I2C22.1, R157.2
unnamed: C315.1, C320.1, U89.11
unnamed: R160.1, U91.5
unnamed: PWR22.1, R155.1
unnamed: D89.A, R155.2
unnamed: C323.1, U93.1
unnamed: C323.2, U93.16
unnamed: I2C23.3, R163.2
unnamed: I2C23.1, R164.2
unnamed: C329.1, C334.1, U93.11
unnamed: R167.1, U95.5
unnamed: PWR23.1, R162.1
unnamed: D93.A, R162.2
PAA_!CS!: U1.3, U3.10
PAA_!CS!1: U5.3, U7.10
PAA_!CS!2: U9.3, U11.10
PAA_!CS!3: U13.3, U15.10
PAA_!CS!4: U17.3, U19.10
PAA_!CS!5: U21.3, U23.10
PAA_!CS!6: U25.3, U27.10
PAA_!CS!7: U29.3, U31.10
PAA_!CS!8: U33.3, U35.10
PAA_!CS!9: U37.3, U39.10
PAA_!CS!10: U41.3, U43.10
PAA_!CS!11: U45.3, U47.10
PAA_!CS!12: U49.3, U51.10
PAA_!CS!13: U53.3, U55.10
PAA_!CS!14: U57.3, U59.10
PAA_!CS!15: U61.3, U63.10
PAA_!CS!16: U65.3, U67.10
PAA_!CS!17: U69.3, U71.10
PAA_!CS!18: U73.3, U75.10
PAA_!CS!19: U77.3, U79.10
PAA_!CS!20: U81.3, U83.10
PAA_!CS!21: U85.3, U87.10
PAA_!CS!22: U89.3, U91.10
PAA_!CS!23: U93.3, U95.10
PAA_!RST!: U1.2, U3.9
PAA_!RST!1: U5.2, U7.9
PAA_!RST!2: U9.2, U11.9
PAA_!RST!3: U13.2, U15.9
PAA_!RST!4: U17.2, U19.9
PAA_!RST!5: U21.2, U23.9
PAA_!RST!6: U25.2, U27.9
PAA_!RST!7: U29.2, U31.9
PAA_!RST!8: U33.2, U35.9
PAA_!RST!9: U37.2, U39.9
PAA_!RST!10: U41.2, U43.9
PAA_!RST!11: U45.2, U47.9
PAA_!RST!12: U49.2, U51.9
PAA_!RST!13: U53.2, U55.9
PAA_!RST!14: U57.2, U59.9
PAA_!RST!15: U61.2, U63.9
PAA_!RST!16: U65.2, U67.9
PAA_!RST!17: U69.2, U71.9
PAA_!RST!18: U73.2, U75.9
PAA_!RST!19: U77.2, U79.9
PAA_!RST!20: U81.2, U83.9
PAA_!RST!21: U85.2, U87.9
PAA_!RST!22: U89.2, U91.9
PAA_!RST!23: U93.2, U95.9
PAA_MOTION: U1.7, U3.12
PAA_MOTION1: U5.7, U7.12
PAA_MOTION2: U9.7, U11.12
PAA_MOTION3: U13.7, U15.12
PAA_MOTION4: U17.7, U19.12
PAA_MOTION5: U21.7, U23.12
PAA_MOTION6: U25.7, U27.12
PAA_MOTION7: U29.7, U31.12
PAA_MOTION8: U33.7, U35.12
PAA_MOTION9: U37.7, U39.12
PAA_MOTION10: U41.7, U43.12
PAA_MOTION11: U45.7, U47.12
PAA_MOTION12: U49.7, U51.12
PAA_MOTION13: U53.7, U55.12
PAA_MOTION14: U57.7, U59.12
PAA_MOTION15: U61.7, U63.12
PAA_MOTION16: U65.7, U67.12
PAA_MOTION17: U69.7, U71.12
PAA_MOTION18: U73.7, U75.12
PAA_MOTION19: U77.7, U79.12
PAA_MOTION20: U81.7, U83.12
PAA_MOTION21: U85.7, U87.12
PAA_MOTION22: U89.7, U91.12
PAA_MOTION23: U93.7, U95.12
PICO: U1.5, U2.14, U3.7
PICO1: U5.5, U6.14, U7.7
PICO2: U9.5, U10.14, U11.7
PICO3: U13.5, U14.14, U15.7
PICO4: U17.5, U18.14, U19.7
PICO5: U21.5, U22.14, U23.7
PICO6: U25.5, U26.14, U27.7
PICO7: U29.5, U30.14, U31.7
PICO8: U33.5, U34.14, U35.7
PICO9: U37.5, U38.14, U39.7
PICO10: U41.5, U42.14, U43.7
PICO11: U45.5, U46.14, U47.7
PICO12: U49.5, U50.14, U51.7
PICO13: U53.5, U54.14, U55.7
PICO14: U57.5, U58.14, U59.7
PICO15: U61.5, U62.14, U63.7
PICO16: U65.5, U66.14, U67.7
PICO17: U69.5, U70.14, U71.7
PICO18: U73.5, U74.14, U75.7
PICO19: U77.5, U78.14, U79.7
PICO20: U81.5, U82.14, U83.7
PICO21: U85.5, U86.14, U87.7
PICO22: U89.5, U90.14, U91.7
PICO23: U93.5, U94.14, U95.7
POCI: U1.4, U2.1, U3.11
POCI1: U5.4, U6.1, U7.11
POCI2: U9.4, U10.1, U11.11
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
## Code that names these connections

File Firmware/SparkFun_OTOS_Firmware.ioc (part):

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Mcu.Name=STM32C011F(4-6)Ux
Mcu.Package=UFQFPN20
Mcu.UserName=STM32C011F6Ux
PA0.GPIOParameters=GPIO_Label
PA0.GPIO_Label=MEAS_1V8
PA0.Mode=IN0
PA0.Signal=ADC1_IN0
PA1.Mode=Full_Duplex_Master
PA1.Signal=SPI1_SCK
PA13.Mode=Serial_Wire
PA13.Signal=DEBUG_SWDIO
PA14-BOOT0.Mode=Serial_Wire
PA14-BOOT0.Signal=DEBUG_SWCLK
PA2.Mode=Full_Duplex_Master
PA2.Signal=SPI1_MOSI
PA3.GPIOParameters=GPIO_Label
PA3.GPIO_Label=LSM_INT
PA3.Signal=GPXTI3
PA4.GPIOParameters=GPIO_Label
PA4.GPIO_Label=PAA_RST
PA4.Signal=GPIO_Output
PA5.GPIOParameters=GPIO_Label
PA5.GPIO_Label=PAA_CS
PA5.Signal=GPIO_Output
PA6.Mode=Full_Duplex_Master
PA6.Signal=SPI1_MISO
PA7.GPIOParameters=GPIO_Label
PA7.GPIO_Label=PAA_MOTION
PA7.Signal=GPIO_Input
PA8.GPIOParameters=PinState,GPIO_Label
PA8.GPIO_Label=LSM_CS
PA8.PinState=GPIO_PIN_SET
PA8.Signal=GPIO_Output
PA9\ [PA11].Signal=GPIO_Output
PB6.Mode=I2C
PB6.Signal=I2C1_SCL
PB7.Mode=I2C
PB7.Signal=I2C1_SDA
PC14-OSCX_IN\ (PC14).GPIOParameters=PinState,GPIO_Label
PC14-OSCX_IN\ (PC14).GPIO_Label=PAA_POW
PC14-OSCX_IN\ (PC14).PinState=GPIO_PIN_SET
PC14-OSCX_IN\ (PC14).Signal=GPIO_Output
PC15-OSCX_OUT\ (PC15).GPIOParameters=PinState,GPIO_Label
PC15-OSCX_OUT\ (PC15).GPIO_Label=VCSEL_POW
PC15-OSCX_OUT\ (PC15).PinState=GPIO_PIN_SET
PC15-OSCX_OUT\ (PC15).Signal=GPIO_Output
RCC.HSE_VALUE=8000000
RCC.SYSCLKFreq_VALUE=48000000
board=custom

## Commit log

2024-01-02 Add library file
2024-01-02 Add initial hardware design
2024-01-02 Add STM32 docs
2024-01-02 Add LSM6DSO datasheet
2024-01-04 PAA5160 footprint tweaks
    Adjust pads to match datasheet recommendations
    Reduce silk outline to be only in corners
    Add tDocu lines for sensor location and pin 1 indication
    Also remove pullup resistor on the STM reset net, the STM has an internal pullup
2024-01-05 v02 update
    Add MOSFETs controlled by GPIO pins in order to supply power to PAA5160 with correct timings
    Add correct decoupling capacitors
    Rearrange some GPIO pins
    Reduce silk around STM32C0
    Reroute entire board 🙃
2024-01-08 Improve GND pour
    Add GND vias
    Nudge via locations to dodge silkscreen better
2024-01-09 Design review updates
    Add regulator name to section in schematic
    Add voltage ranges for each component, and required voltage range for entire board
    Add GND via next to STM32 GND pad
    Center traces between Q1 and R2
    Nudge via and 3.3V trace left of R6 to get better GND stitching
    Fix acid trap with via under U4
2024-01-09 Improve GND pour
    Nudge up 3.3V trace left of C5 to get GND to pour below it
2024-01-09 Add pulldown resistor to BOOT0 pin
2024-01-09 Add axes to PAA5160 tDocu
2024-02-23 Initial pass of docs
2024-02-26 v10 updates
    Bump version number to v10
    Add external pullup to RST net
    Nudge components and traces away from mounting holes
    Replace 3.3V regulator with 1.8V version
    Add PROD_ID values to STM32C0 and PAA5160
    Rename PAA5160 to full name of PAA5160E1-Q
2024-02-26 Update section titles in schematic
2024-02-26 Replace external reset pullup with decoupling cap
    Turns out the datasheet calls for it, whoops!
2024-02-28 Design review updates
    Fix one via being the wrong size
    Add silk line between R6 and C3
2024-02-28 Add v10 production files
2024-02-29 Updating names and overview
2024-03-04 Fix STM32C0 PROD_ID
2024-03-15 Minor name changes
2024-03-22 Link updates
2024-03-26 Updates to example page
2024-03-29 Stubs for arduino examples
2024-04-08 FIRST Tech Challenge updates
2024-04-22 Example menu images
2024-04-22 Fix sizing on images
2024-04-22 v11 updates
    Bump version number to v11
    Fix PAA5160 footprint (pad pitch was 0.6mm instead of 0.65mm, and needed to be pushed out 0.1mm)
    Fix power LED orientation (doh!)
    Fix measures
2024-04-22 Add default I2C address to schematic
2024-04-25 Add v11 production files
2024-05-07 Updating hardware and a few examples
2024-05-07 Fix board outline file
2024-05-23 Updating examples
2024-05-24 Updating to examples, hardware assembly
2024-05-24 Updates per Dryw
2024-05-27 Updates to products and single page
2024-05-27 Updating ReadMe
2024-05-28 Adding troubleshooting notes and rearranging pages
2024-05-28 Adding feature photo and updating example working
2024-05-28 Add v1.0 firmware
2024-05-29 Adding Visualization Script
2024-05-29 Fixing link to instructions
2024-05-30 Adding XRP Icon and updating examples
2024-05-30 Adding "Coming Soon" pages to yml
2024-05-30 Updated verbiage
2024-05-30 Adding scripts/libraries/etc
2024-05-30 Add register map
2024-05-30 Update reference to latest firmware
2024-05-30 Adding product video and links to register map
2024-05-31 Add Kalman filter design documents
2024-05-31 Add lookup table calibration documentation
2024-06-12 Python and Java(FTC) software setup changes
2024-06-12 Update single_page.md
    Fixing copy/paste error
2024-06-17 Deployed d894333 with MkDocs version: 1.6.0
2024-07-03 Adding RPi Bookworm note
2024-07-24 Updating per Dryw
    v9.2 of the SDK includes Java - updating verbiage to reflect
2024-08-06 Deployed aeb660d with MkDocs version: 1.6.0
2024-08-13 Updating Python Examples
2024-08-13 Deployed 3501e48 with MkDocs version: 1.6.0
2024-11-15 Deployed 17a836a with MkDocs version: 1.6.1
2025-02-20 fix readme image - lost due to magento change over
2025-02-20 Deployed 6769777 with MkDocs version: 1.6.1
2025-08-20 Improve offset documentation
2025-08-20 Updating GH pages build file
    Upading GitHub pages build .yml files from old version.
2025-08-20 Deployed dcb7f29 with MkDocs version: 1.6.1
2025-08-25 Minor docs edit
    Fixing hyperlink render issue.
2025-08-25 Deployed 20ca2d9 with MkDocs version: 1.6.1
2026-06-03 Deployed 5925ace with MkDocs version: 1.6.1
